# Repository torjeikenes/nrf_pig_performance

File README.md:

# NRF Pig Performance

An activity tracker for pigs consisting of a BLE earchip for each pig, and a sentral that gathers data from each pig over BLE and sends it to the backend over NB-IoT.

Link to code for website: https://github.com/alfhj/pig-performance

## Setup

Download nrf5 SDK v. 12.3.0 into the root folder of the repo
https://www.nordicsemi.com/Products/Development-software/nRF5-SDK/Download

### Install Arm GNU Toolchain

https://lindevs.com/install-arm-gnu-toolchain-on-ubuntu

I had some problems with 12.2, so I use version 11.3.1 (as of 28/2/23)

`ARM_TOOLCHAIN_VERSION=11.3.Rel1`

`curl -Lo gcc-arm-none-eabi.tar.xz "https://developer.arm.com/-/media/Files/downloads/gnu/${ARM_TOOLCHAIN_VERSION}/binrel/arm-gnu-toolchain-${ARM_TOOLCHAIN_VERSION}-x86_64-arm-none-eabi.tar.xz"`

`sudo mkdir /opt/gcc-arm-none-eabi`

`sudo tar xf gcc-arm-none-eabi.tar.xz --strip-components=1 -C /opt/gcc-arm-none-eabi`

Add `export PATH=$PATH:/opt/gcc-arm-none-eabi/bin` to `.bashrc` or `.zshrc`

Open `<SDK_ROOT>/components/toolchain/gcc/Makefile.posix` and set the correct path

### Install nrf command line tools

https://www.nordicsemi.com/Products/Development-tools/nrf-command-line-tools/download

## Build

For nrf51 dk open pca10028/s130/armgcc in the terminal and build using the Makefile.

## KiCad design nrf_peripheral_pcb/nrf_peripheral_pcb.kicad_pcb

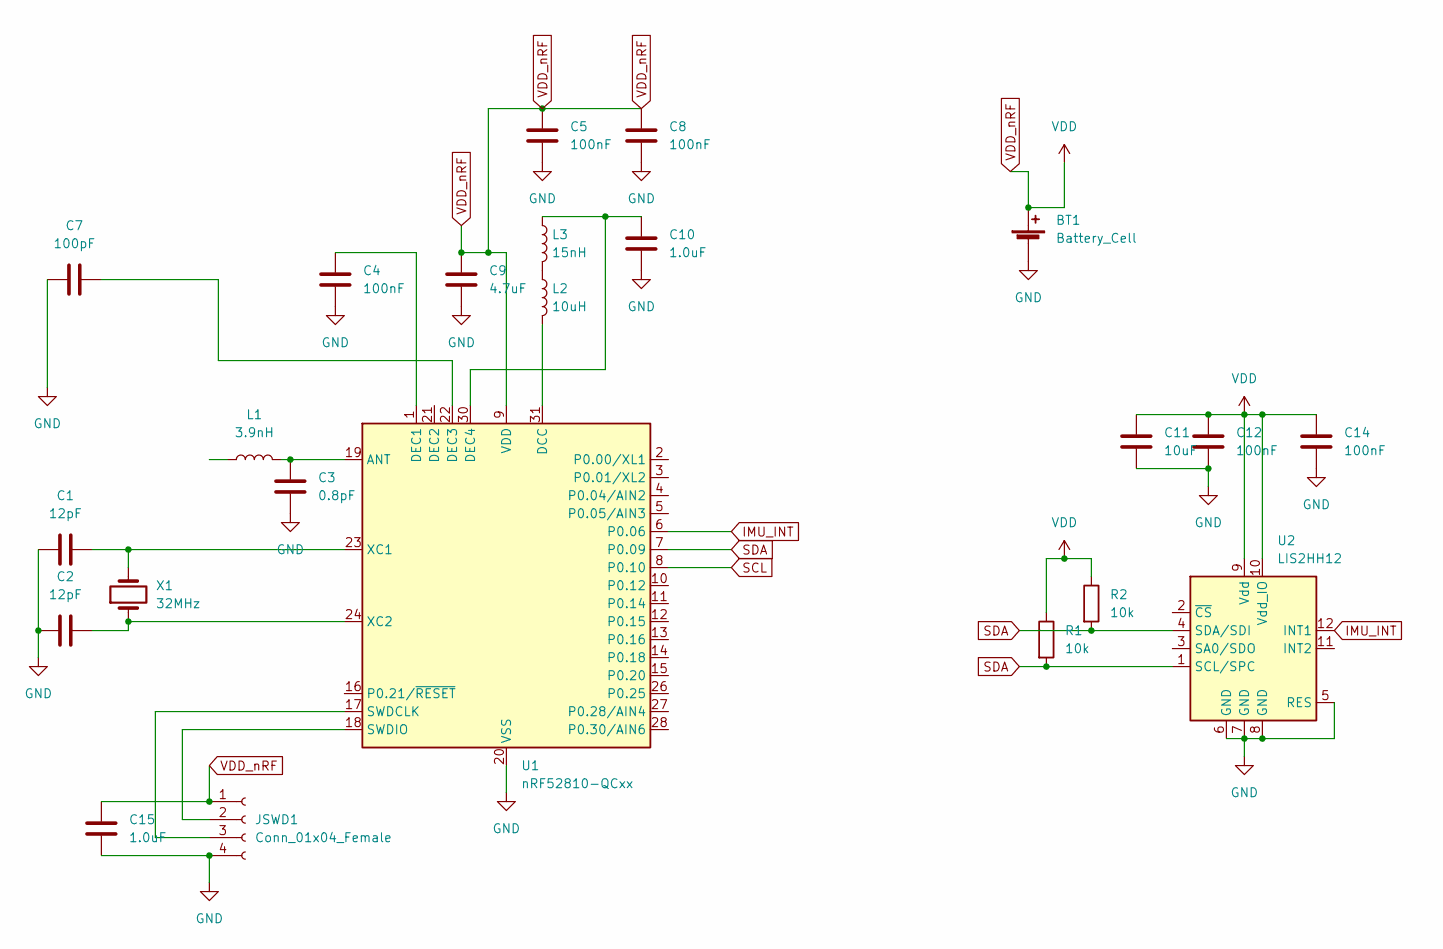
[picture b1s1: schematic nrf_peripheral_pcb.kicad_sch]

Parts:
BT1: Battery_Cell; BatteryHolder_Keystone_3002_1x2032
C1, C2: 12pF; C_0402_1005Metric
C3: 0.8pF; C_0402_1005Metric
C4, C5, C8: 100nF; C_0402_1005Metric
C7: 100pF; C_0402_1005Metric
C9: 4.7uF; C_0603_1608Metric
C10, C15: 1.0uF; C_0603_1608Metric
C11: 10uF; C_0603_1608Metric
C12, C14: 100nF; C_0603_1608Metric
JSWD1: Conn_01x04_Female; PinHeader_1x04_P1.27mm_Horizontal
L1: 3.9nH; L_0402_1005Metric
L2: 10uH; L_0603_1608Metric
L3: 15nH; L_0402_1005Metric
R1, R2: 10k; R_0603_1608Metric
U1: nRF52810-QCxx; QFN-32-1EP_5x5mm_P0.5mm_EP3.6x3.6mm
U2: LIS2HH12; LGA-12_2x2mm_P0.5mm
X1: 32MHz; Crystal_SMD_2016-4Pin_2.0x1.6mm

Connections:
GND: BT1.2 (-), C1.1, C2.1, C3.2, C4.2, C5.2, C7.1, C8.2, C9.2, C10.2, C11.1, C12.1, C14.1, C15.1, JSWD1.4, U1.20 (VSS), U1.29 (VSS), U1.33 (VSS), U2.5 (RES), U2.6 (GND), U2.7 (GND), U2.8 (GND)
IMU_INT: U1.6 (P0.06), U2.12 (INT1)
unnamed: C4.1, U1.1 (DEC1)
unnamed: C7.2, U1.22 (DEC3)
unnamed: JSWD1.2, U1.18 (SWDIO)
unnamed: JSWD1.3, U1.17 (SWDCLK)
unnamed: C3.1, L1.2, U1.19 (ANT)
unnamed: L2.2, U1.31 (DCC)
unnamed: C10.1, L3.1, U1.30 (DEC4)
unnamed: L2.1, L3.2
unnamed: C2.2, U1.24 (XC2), X1.1
unnamed: C1.2, U1.23 (XC1), X1.2
SCL: U1.8 (P0.10)
SDA: R1.2, R2.2, U1.7 (P0.09), U2.1 (SCL/SPC), U2.4 (SDA/SDI)
VDD_nRF: BT1.1 (+), C5.1, C8.1, C9.1, C11.2, C12.2, C14.2, C15.2, JSWD1.1, R1.1, R2.1, U1.9 (VDD), U1.25 (VDD), U1.32 (VDD), U2.9 (Vdd), U2.10 (Vdd_IO)

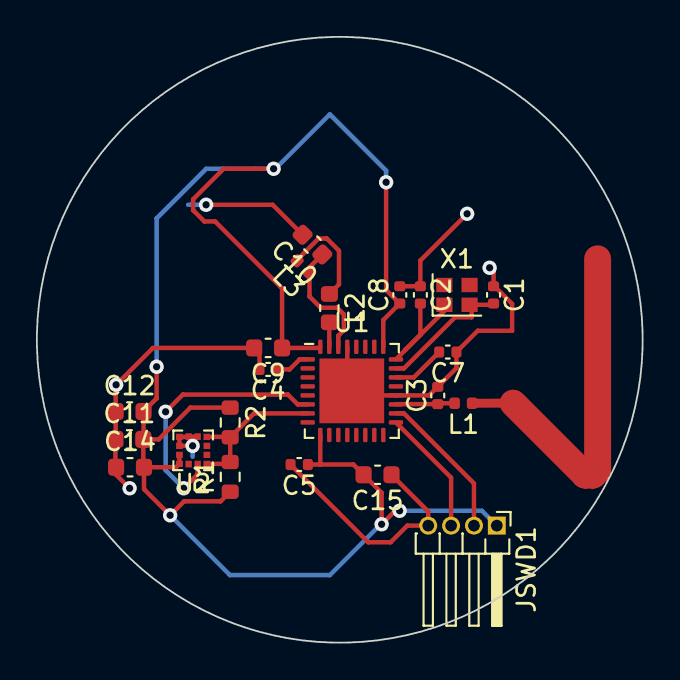
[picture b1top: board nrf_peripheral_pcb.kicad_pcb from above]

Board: 2 copper layers, 33.7 x 33.7 mm, 23 parts (1 on the bottom side), 14 nets.

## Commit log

2023-02-23 Reads from mpu6050
2023-02-28 Started setting up motion detection interrupt
2023-02-28 removed submodule
2023-02-28 Added readme
2023-02-28 setup interrupt
2023-02-28 add .vscode files
2023-02-28 add vscode
2023-02-28 Enabled logging
2023-03-01 settings
2023-03-01 Interrupt works
2023-03-01 Send data as char string
2023-03-01 Moved motion detection init to another function
2023-03-01 used motion detection init in main
2023-03-02 added ble_uart_central example
2023-03-02 Made pcb
2023-03-08 Add pcb prices
2023-03-08 try summing data
2023-03-15 Sending works between pig and hub
2023-03-22 updated gitignore
2023-03-22 Sending to arduino works
2023-03-22 cleanup
2023-03-22 started from uart example for nrf52
2023-03-22 modified for dongle
2023-03-22 revert
2023-04-11 pcb changes
2023-04-11 format
2023-04-11 started timer implementation
2023-04-11 enabled timer
2023-04-12 changed time
2023-04-12 added timer
2023-04-12 Send data as bytes instead of converting to string
2023-04-12 print as hex
2023-04-15 flashes to nrf52 dongle
2023-04-15 changed to app_timer
2023-04-15 send data every 60s
2023-04-15 reduced threshold
2023-04-15 cleanup code
2023-04-15 changed threshold
2023-04-15 småpirk
2023-04-19 changed pcb size
2023-05-03 removed unused project
2023-05-03 Moved arduino code to this repo
